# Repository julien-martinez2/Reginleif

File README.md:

# 🕷️ Reginleif — Autonomous Quadruped Walking Robot

[-green.svg)]()

> A custom-engineered, distributed quadruped combat walker inspired by the **XM2 Reginleif** and **M1A4 Juggernaut** from the acclaimed light novel & anime series ***86 - Eighty Six***.

---

## 📖 Table of Contents

- [Motivation & Inspiration](#-motivation--inspiration)
- [System Architecture](#-system-architecture)
  - [Functional Architecture](#functional-architecture)
  - [Technical & Electrical Architecture](#technical--electrical-architecture)
- [Hardware & Key Components](#-hardware--key-components)
  - [Sun Board (Central Controller)](#sun-board)
  - [Planet Boards (Legs Controllers)](#planet-boards)
  - [Moon Boards (Angle Sensors)](#moon-boards)
  - [Dual-Encoder Sensing Strategy](#dual-encoder-sensing-strategy)
- [Firmware Architecture](#-firmware-architecture)
  - [NVIC Preemptive Priority Hierarchy](#nvic-preemptive-priority-hierarchy)
  - [Real-Time Timer Scheduling](#real-time-timer-scheduling)
  - [Zero-CPU UART DMA with IDLE Line Detection](#zero-cpu-uart-dma-with-idle-line-detection)
- [Project Documentation & CAD Assets](#-project-documentation--cad-assets)
- [Roadmap & Deliverables](#-roadmap--deliverables)
- [Author & Community](#-author--community)
- [License](#-license)

---

## 💡 Motivation & Inspiration

The goal of this project is to take the agility, distinctive gait mechanics, and rugged aesthetic of the **XM2 Reginleif** from *86 - Eighty Six* and bring it into physical reality.

Building a multi-jointed legged walker from scratch serves as an end-to-end engineering challenge across multiple disciplines:
1. **Developing Real-Time Embedded Skills:** Mastering bare-metal ARM Cortex-M control, deterministic task scheduling, multi-bus SPI synchronization, and DMA streaming.
2. **Custom PCB & Power Electronics:** Designing compact 4-layer PCBs, handling thermal dissipation, power distribution for 16 simultaneous DC gearmotors, and integrated eFuse circuit protection.
3. **Complex Kinematics & Robotics:** Solving 3D inverse kinematics, gait generation, and closed-loop position control with mechanical backlash compensation.

**Open Source Philosophy:** Advanced quadruped robotics often relies on expensive off-the-shelf smart actuators or proprietary platforms. By documenting every schematic, trade-off, calculation, and line of code, this repository aims to serve as a practical, open reference for robotics students, engineers, and hobbyists building their own legged systems.

---

## 🏛️ System Architecture

### Functional Architecture

The robot employs a **hierarchical distributed architecture**, offloading high-frequency motor control to dedicated microcontrollers while centralizing planning, telemetry, and stabilization:

```
                      ┌────────────────────────────────────────┐
                      │        High-Level Intelligence         │
                      │     Raspberry Pi (Vision, Autonomy)    │
                      └──────────────────┬─────────────────────┘
                                         │ SPI / UART
                                         ▼
                      ┌────────────────────────────────────────┐
                      │    Central Master MCU ("Sun Board")    │
                      │  • IMU Body Stabilization (BNO086)     │
                      │  • Power Distribution & Battery Monitor│
                      │  • Master Gait Coordinator             │
                      └──────────────────┬─────────────────────┘
                                         │
          ┌──────────────────────────────┼──────────────────────────────┐
          │ RS-485 Differential Bus      │ (Master-Slave Protocol)      │
          ▼                              ▼                              ▼
 ┌──────────────────┐           ┌──────────────────┐           ┌──────────────────┐
 │  Planet Board 1  │           │  Planet Board 2  │           │ Planet Boards 3-4│
 │ (STM32G031)      │           │ (STM32G031)      │           │  (STM32G031)     │
 │ 4x N20 Motors    │           │ 4x N20 Motors    │           │ 4x N20 Motors    │
 └──────────────────┘           └──────────────────┘           └──────────────────┘
          │                     SPI Bus  │ (Master-Slave Protocol)      │
          ▼                              ▼                              ▼
 ┌──────────────────┐           ┌──────────────────┐           ┌──────────────────┐
 │ Moon Boards 1-4  │           │ Moon Boards 5-8  │           │ Moon Boards 9-16 │
 │ (MA730 Abs.)     │           │ (MA730 Abs.)     │           │ (MA730 Abs.)     │
 └──────────────────┘           └──────────────────┘           └──────────────────┘

```

---

### Technical & Electrical Architecture

```
                              [ 3S LiPo Battery (11.1V - 12.6V) ]
                                              │
                                              ▼
                                 [ TPS259827 15A eFuse ]
                                (UVLO Cutoff at 10.83V)
                                              │
                  ┌───────────────────────────┼───────────────────────────┐
                  │ VM (12V) Motor Power      │                           │
                  ▼                           ▼                           ▼
        ┌───────────────────┐       ┌───────────────────┐       ┌──────────────────────┐
        │ AP63205 (5V Buck) │       │ AP63203 (3.3V)    │       │ TPS22919 Load SW     │
        │ -> Raspberry Pi   │       │ -> Sun Board MCU  │       │ -> Planet Board VDD  │
        └───────────────────┘       └───────────────────┘       └─────────┬────────────┘
                                                                          │
                                  ┌───────────────────────────────────────┘
                                  │ 5-Pin JST-PA Harness (12V, 3.3V, GND, RS485_A/B)
                                  ▼
         ┌─────────────────────────────────────────────────────────────────┐
         │                     MODULAR PLANET BOARD (x4)                   │
         │                                                                 │
         │   [ THVD1406 RS-485 ] <── UART DMA ──> [ STM32G031 MCU ]        │
         │                                              │                  │
         │              ┌───────────────────────────────┴────────┐         │
         │              ▼ (SPI1 Bus)                             ▼ (SPI2)  │
         │     [ 4x MA730 Encoders ]                       [ DRV8908 ]     │
         │     Absolute Joint Angles                   8x Half-Bridges     │
         │     (Diametric Magnets)                               │         │
         │              ▲                                        ▼         │
         │              │ Joint Output Shaft              4x CHF-GW12T-N20 │
         │              └──────────────────────────────── (302:1 Worm)     │
         │                                                       │         │
         │   [ Incremental Encoders ] <── EXTI (PA0, PB1, PB3, PC14) ─────┘│
         └─────────────────────────────────────────────────────────────────┘

```

---

## 🛠️ Hardware & Key Components

### Sun Board
- **Master Processing:** STM32G031 / Raspberry Pi pairing for autonomous operation, telemetry streaming, and wireless communication.
- **Power & Circuit Protection:**
  - **TPS259827 15A eFuse:** Ultra-fast short-circuit protection and hardware programmable undervoltage lockout (V_UVLO = 10.83 V), preventing 3S LiPo over-discharge).
  - **AP63205 & AP63203:** High-efficiency synchronous buck converters generating 5 V (logic/SBC) and 3.3 V (peripherals).
  - **TPS22919 Load Switches:** Independent hardware-level logic power isolation and current limiting for each peripheral board.
- **Inertial Measurement:** **BNO086** 9-axis sensor fusion IMU over SPI for real-time body attitude stabilization.

### Planet Boards
- **Dedicated MCU:** **STM32G031G8U6** (ARM Cortex-M0+ running at 16 MHz, 4-layer compact layout with solid internal ground planes).
- **Motor Driver:** **DRV8908** automotive-grade 8 half-bridge driver, providing 4 fully independent bi-directional motor channels with individual hardware current limiting and fault telemetry.
- **Bus Transceiver:** **THVD1406DR** RS-485 transceiver with auto-direction sensing, eliminating the need for half-duplex DE/RE switching overhead.
- **Connectors:** JST-PA (power and differential communication) and JST-ZH (motor and sensor interconnects).

### Moon Boards
- **Angle Sensor:** MA730 is a magnetic angle sensor, which is placed next to the shaft of the motor on which a magnet is put.
- **Connectors:** JST-ZH (same as the motors).

---

### Dual-Encoder Sensing Strategy

Miniature worm gearboxes provide high stall torque and self-locking capabilities, but introduce mechanical backlash. To solve this, a dual-encoder feedback architecture is implemented:

| Sensor Type | Part & Interface | Resolution | Placement | Role in Control Loop |
| :--- | :--- | :--- | :--- | :--- |
| **Incremental Magnetic Encoder** | 2-Phase Hall (EXTI) | 2x Quadrature (~2107 counts/rev on motor shaft) | Motor Tail Shaft | **High-frequency velocity estimation** and instantaneous PID rate control. |
| **Absolute Magnetic Encoder** | **MA730GQ-Z** (SPI1) | 14-bit (16,384 counts/rev) | Output Joint Shaft (with Diametric Ring Magnets) | **Absolute angle calibration (10 Hz)** to eliminate gearbox play, backlash, and drift. |

---

## 💻 Firmware Architecture

### NVIC Preemptive Priority Hierarchy

The Cortex-M0+ interrupt controller is prioritized to guarantee that critical hardware signals and high-speed encoder transitions are never delayed by slower math computations:

```

Priority 0 (Highest) ──► SysTick & EXTI Lines (PA0, PB1, PB3, PC14, PA2 nFAULT)
│
Priority 1             ──► USART1 Communication & DMA Channels
│
Priority 2             ──► TIM2 (DRV8908 SPI Updates) & TIM3 (MagAlpha SPI Reads)
│
Priority 3 (Lowest)    ──► TIM1 (Software Inverse Kinematics & PID Loops)

```

- **Zero-Jitter Pulse Counting:** Encoders run at Priority 0 so wheel pulses are captured without dropped ticks during motor acceleration.
- **Fault Handling:** The open-drain `nFAULT` pin on `PA2` triggers an immediate shutdown sequence on overcurrent or thermal warnings.
- **Safe Preemption:** Heavy inverse kinematics floating-point calculations (Priority 3) safely yield execution whenever a peripheral event occurs.

---

### Real-Time Timer Scheduling

| Timer | Execution Frequency | Period | Task Description |
| :--- | :--- | :--- | :--- |
| **EXTI Lines** | Asynchronous | < 1 µs | Hardware edge-triggered incremental encoder decoding (Motors 1–4). |
| **TIM3** | **10 Hz** | 100 ms | SPI1 sequential polling of the 4 joint-level MA730 absolute encoders. |
| **TIM2** | **50 Hz** | 20 ms | SPI2 multi-channel register write updating DRV8908 motor PWM/directions. |
| **TIM1** | **20 Hz - 50 Hz** | 20 - 50 ms | Inverse kinematics trajectory solving, PID position/velocity loop execution. |

---

### Zero-CPU UART DMA with IDLE Line Detection

Communication between the central master board and the leg modules uses DMA combined with hardware IDLE line detection (`HAL_UARTEx_ReceiveToIdle_DMA`):

```cpp
// Non-blocking packet reception
void HAL_UARTEx_RxEventCallback(UART_HandleTypeDef *huart, uint16_t Size) {
    if (huart->Instance == USART1) {
        // Validate header and packet checksum
        if (Size >= 11 && rx_buffer[0] == 0xAA && rx_buffer[1] == 0x55) {
            ParseMasterCommand(rx_buffer, Size);
        }
        // Immediately re-arm DMA reception for the next packet
        HAL_UARTEx_ReceiveToIdle_DMA(&huart1, rx_buffer, RX_BUFFER_SIZE);
    }
}

```

* **Zero CPU overhead** while bytes are on the wire.
* The MCU triggers a single interrupt only after an entire variable-length packet is delivered and the bus goes idle.

---

## 📂 Project Documentation & CAD Assets

All schematics, BOMs, mechanical studies, and test records are available in the repository:

* **Hardware Schematics & KiCad Layouts:** 4-layer Leg Board, Satellite Angle Sensor PCBs, and Central Carrier Board.
* **Mechanical CAD:** 3D printed joint housings, worm gearbox mounts, and chassis brackets.

---

## 🗺️ Roadmap & Deliverables

* [x] Functional specification and torque/power feasibility study
* [x] 4-layer Leg Board PCB design and component assembly (KiCad)
* [ ] Mechanical Design and 3D-printing (FreeCAD)
* [ ] Bare-metal firmware setup (CubeMX, SPI1/SPI2, multi-channel EXTI, UART DMA)
* [ ] MA730 absolute magnetic sensor driver (`magalpha.cpp`)
* [ ] DRV8908 8 half-bridge motor controller driver (`drv8908.cpp`)
* [ ] 3D Inverse Kinematics math library and body orientation matrix
* [ ] Dynamic walking gait generation (Crawl, Trot, and Creep gaits)
* [ ] Central Sun Board assembly & BNO086 IMU stabilization loop
* [ ] Auxiliary subsystems: Tilt-axis turret mechanism and deployable anchor system

---

## 👤 Author & Community

Designed and engineered with passion by **Julien Martinez** ([@julien-martinez2](github.com/julien-martinez2)).

If you are working on custom quadruped walkers, legged robotics, or distributed motor controllers, feel free to open an issue, start a discussion, or contribute!

---

## 📄 License

This project is distributed under the **MIT License**. See [`LICENSE`](https://www.google.com/search?q=LICENSE) for more details.

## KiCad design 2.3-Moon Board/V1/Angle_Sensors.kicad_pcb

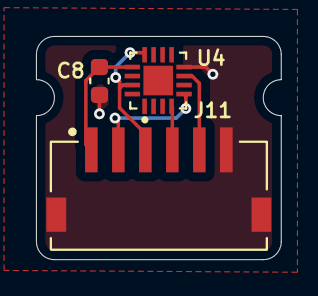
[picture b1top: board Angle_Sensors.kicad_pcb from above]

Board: 4 copper layers, 13.6 x 12.4 mm, 3 parts (0 on the bottom side), 6 nets.

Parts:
C8: 1uF; C_0603_1608Metric
J11: S6B-ZR-SM4-TF; JST_S6B-ZR-SM4A-TF_LF__SN_
U4: MA730GQ-Z_1; QFN50P300X300X100-17N

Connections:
+3.3V: C8.1, J11.1, U4.13 (VDD)
GND: C8.2, J11.6, J11.SH1 (SHIELD), J11.SH2 (SHIELD), U4.8 (GND)
unnamed: J11.2, U4.5 (CS)
unnamed: J11.5, U4.7 (MISO)
unnamed: J11.4, U4.4 (MOSI)
unnamed: J11.3, U4.12 (SCLK), U4.15 (SSCK)

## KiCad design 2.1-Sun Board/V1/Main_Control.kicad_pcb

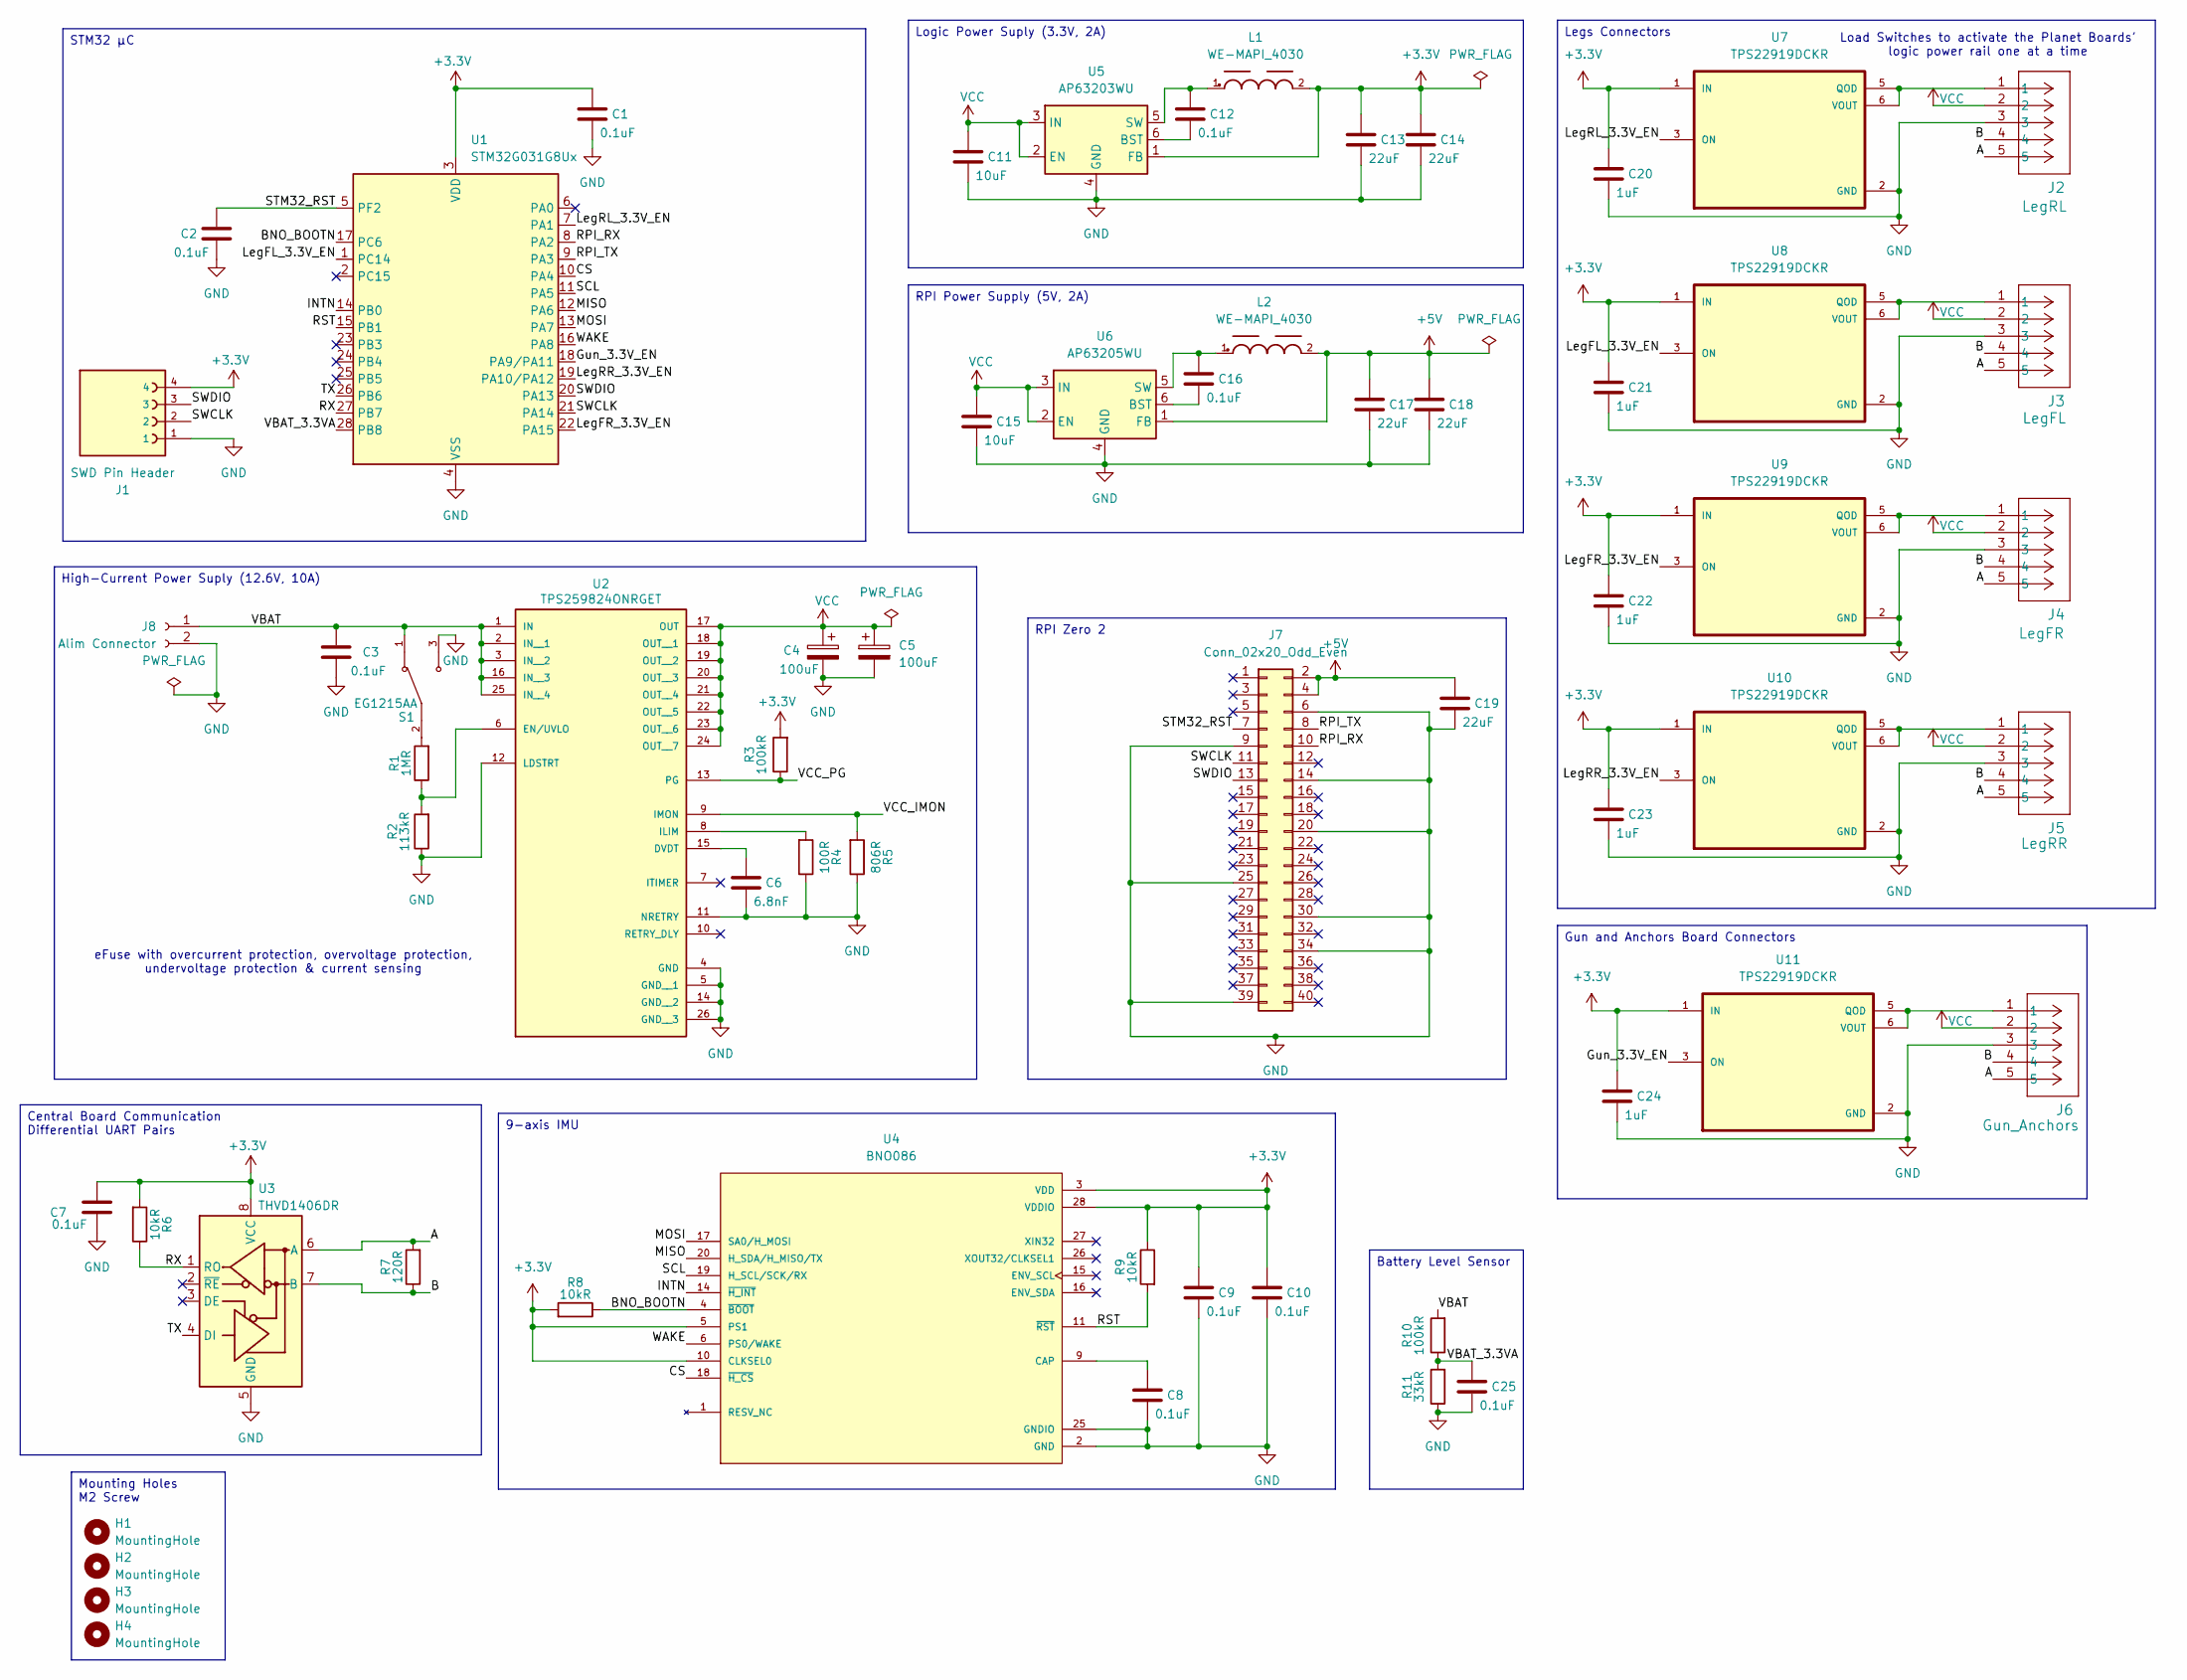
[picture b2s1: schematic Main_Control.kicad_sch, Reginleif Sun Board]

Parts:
C1, C2, C3, C7, C8, C9, C10, C12, C16, C25: 0.1uF; C_0603_1608Metric
C4, C5: 100uF; CP_EIA-7343-43_Kemet-X
C6: 6.8nF; C_0402_1005Metric
C11, C15: 10uF; C_0603_1608Metric
C13, C14, C17, C18: 22uF; C_0805_2012Metric
C19: 22uF; R_0805_2012Metric
C20, C21, C22, C23, C24: 1uF; C_0402_1005Metric
H1, H2, H3, H4: MountingHole; MountingHole_2.2mm_M2
J1: SWD Pin Header; HARWIN_M20-7910442R
J2: LegRL; SM05B_PASS
J3: LegFL; SM05B_PASS
J4: LegFR; SM05B_PASS
J5: LegRR; SM05B_PASS
J6: Gun_Anchors; SM05B_PASS
J7: Conn_02x20_Odd_Even; PinHeader_2x20_P2.54mm_Vertical_SMD
J8: Alim Connector; SolderWire-0.75sqmm_1x02_P4.8mm_D1.25mm_OD2.3mm_Relief
L1, L2: WE-MAPI_4030
R1: 1MR; R_0402_1005Metric
R2: 113kR; R_0402_1005Metric
R3, R10: 100kR; R_0402_1005Metric
R4: 100R; R_0402_1005Metric
R5: 806R; R_0402_1005Metric
R6, R8, R9: 10kR; R_0603_1608Metric
R7: 120R; R_0402_1005Metric
R11: 33kR; R_0402_1005Metric
S1: EG1215AA; SW_EG1215AA; PARTREV A
U1: STM32G031G8Ux; QFN-28_4x4mm_P0.5mm
U2: TPS259824ONRGET; IC_TPS259824ONRGET; Part_Rev C
U3: THVD1406DR; SOIC-8_3.9x4.9mm_P1.27mm
U4: BNO086; IC_BNO086; PARTREV v1.17
U5: AP63203WU; TSOT-23-6
U6: AP63205WU; TSOT-23-6
U7, U8, U9, U10, U11: TPS22919DCKR; SOT65P210X110-6N

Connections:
+3.3V: C1.1, C7.1, C9.1, C10.1, C13.1, C14.1, C20.1, C21.1, C22.1, C23.1, C24.1, J1.4, L1.2, R3.2, R6.2, R8.2, R9.1, U1.3 (VDD), U3.8 (VCC), U4.3 (VDD), U4.5 (PS1), U4.10 (CLKSEL0), U4.28 (VDDIO), U5.1 (FB), U7.1 (IN), U8.1 (IN), U9.1 (IN), U10.1 (IN), U11.1 (IN)
+5V: C17.1, C18.1, C19.1, J7.2, J7.4, L2.2, U6.1 (FB)
/A: J2.5, J3.5, J4.5, J5.5, J6.5, R7.2, U3.6 (A)
/B: J2.4, J3.4, J4.4, J5.4, J6.4, R7.1, U3.7 (B)
/BNO_BOOTN: R8.1, U1.17 (PC6), U4.4 (~BOOT)
/CS: U1.10 (PA4), U4.18 (~H_CS)
/Gun_3.3V_EN: U1.18 (PA9/PA11), U11.3 (ON)
/INTN: U1.14 (PB0), U4.14 (~H_INT)
/LegFL_3.3V_EN: U1.1 (PC14), U8.3 (ON)
/LegFR_3.3V_EN: U1.22 (PA15), U9.3 (ON)
/LegRL_3.3V_EN: U1.7 (PA1), U7.3 (ON)
/LegRR_3.3V_EN: U1.19 (PA10/PA12), U10.3 (ON)
/MISO: U1.12 (PA6), U4.20 (H_SDA/H_MISO/TX)
/MOSI: U1.13 (PA7), U4.17 (SA0/H_MOSI)
/RPI_RX: J7.10, U1.8 (PA2)
/RPI_TX: J7.8, U1.9 (PA3)
/RST: R9.2, U1.15 (PB1), U4.11 (~RST)
/RX: R6.1, U1.27 (PB7), U3.1 (RO)
/SCL: U1.11 (PA5), U4.19 (H_SCL/SCK/RX)
/STM32_RST: C2.1, J7.7, U1.5 (PF2)
/SWCLK: J1.2, J7.11, U1.21 (PA14)
/SWDIO: J1.3, J7.13, U1.20 (PA13)
/TX: U1.26 (PB6), U3.4 (DI)
/VBAT: C3.1, J8.1, R10.2, S1.1, U2.1 (IN), U2.2 (IN__1), U2.3 (IN__2), U2.16 (IN__3), U2.25 (IN__4), U2.27, U2.28, U2.29, U2.30, U2.31, U2.32
/VBAT_3.3VA: C25.1, R10.1, R11.2, U1.28 (PB8)
/VCC_IMON: R5.2, U2.9 (IMON)
/VCC_PG: R3.1, U2.13 (PG)
/WAKE: U1.16 (PA8), U4.6 (PS0/WAKE)
GND: C1.2, C2.2, C3.2, C4.2, C5.2, C6.2, C7.2, C8.2, C9.2, C10.2, C11.2, C13.2, C14.2, C15.2, C17.2, C18.2, C19.2, C20.2, C21.2, C22.2, C23.2, C24.2, C25.2, J1.1, J2.3, J3.3, J4.3, J5.3, J6.3, J7.6, J7.9, J7.14, J7.20, J7.25, J7.30, J7.34, J7.39, J8.2, R2.1, R4.1, R5.1, R11.1, S1.3, U1.4 (VSS), U2.4 (GND), U2.5 (GND__1), U2.11 (NRETRY), U2.12 (LDSTRT), U2.14 (GND__2), U2.26 (GND__3), U2.33, U2.34, U2.35, U3.5 (GND), U4.2 (GND), U4.25 (GNDIO), U5.4 (GND), U6.4 (GND), U7.2 (GND), U8.2 (GND), U9.2 (GND), U10.2 (GND), U11.2 (GND)
unnamed: R1.2, S1.2
unnamed: C6.1, U2.15 (DVDT)
unnamed: R1.1, R2.2, U2.6 (EN/UVLO)
unnamed: R4.2, U2.8 (ILIM)
unnamed: C8.1, U4.9 (CAP)
unnamed: C12.2, U5.6 (BST)
unnamed: C12.1, L1.1, U5.5 (SW)
unnamed: C16.2, U6.6 (BST)
unnamed: C16.1, L2.1, U6.5 (SW)
unnamed: J2.1, U7.5 (QOD), U7.6 (VOUT)
unnamed: J3.1, U8.5 (QOD), U8.6 (VOUT)
unnamed: J4.1, U9.5 (QOD), U9.6 (VOUT)
unnamed: J5.1, U10.5 (QOD), U10.6 (VOUT)
unnamed: J6.1, U11.5 (QOD), U11.6 (VOUT)
VCC: C4.1, C5.1, C11.1, C15.1, J2.2, J3.2, J4.2, J5.2, J6.2, U2.17 (OUT), U2.18 (OUT__1), U2.19 (OUT__2), U2.20 (OUT__3), U2.21 (OUT__4), U2.22 (OUT__5), U2.23 (OUT__6), U2.24 (OUT__7), U5.2 (EN), U5.3 (IN), U6.2 (EN), U6.3 (IN)

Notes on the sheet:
Load Switches to activate the Planet Boards' logic power rail one at a time
eFuse with overcurrent protection, overvoltage protection, undervoltage protection & current sensing
STM32 µC
RPI Power Supply (5V, 2A)
Legs Connectors
Mounting Holes M2 Screw
Gun and Anchors Board Connectors
Logic Power Suply (3.3V, 2A)
Central Board Communication Differential UART Pairs
9-axis IMU
High-Current Power Suply (12.6V, 10A)
Battery Level Sensor
RPI Zero 2

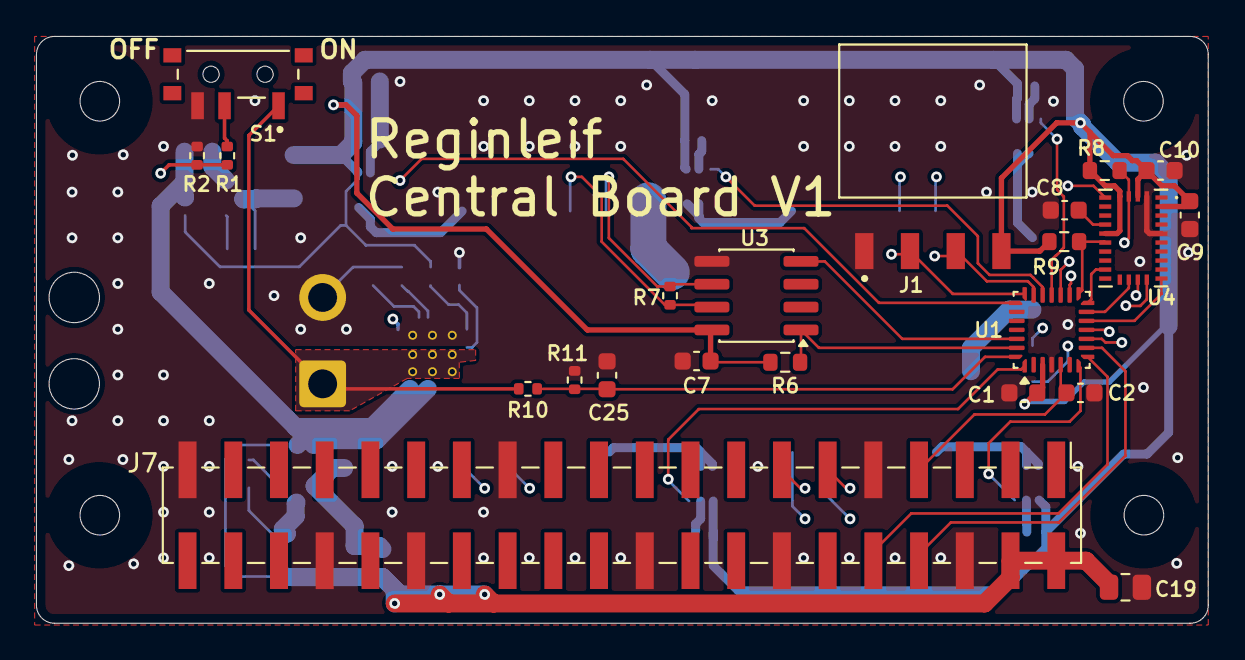
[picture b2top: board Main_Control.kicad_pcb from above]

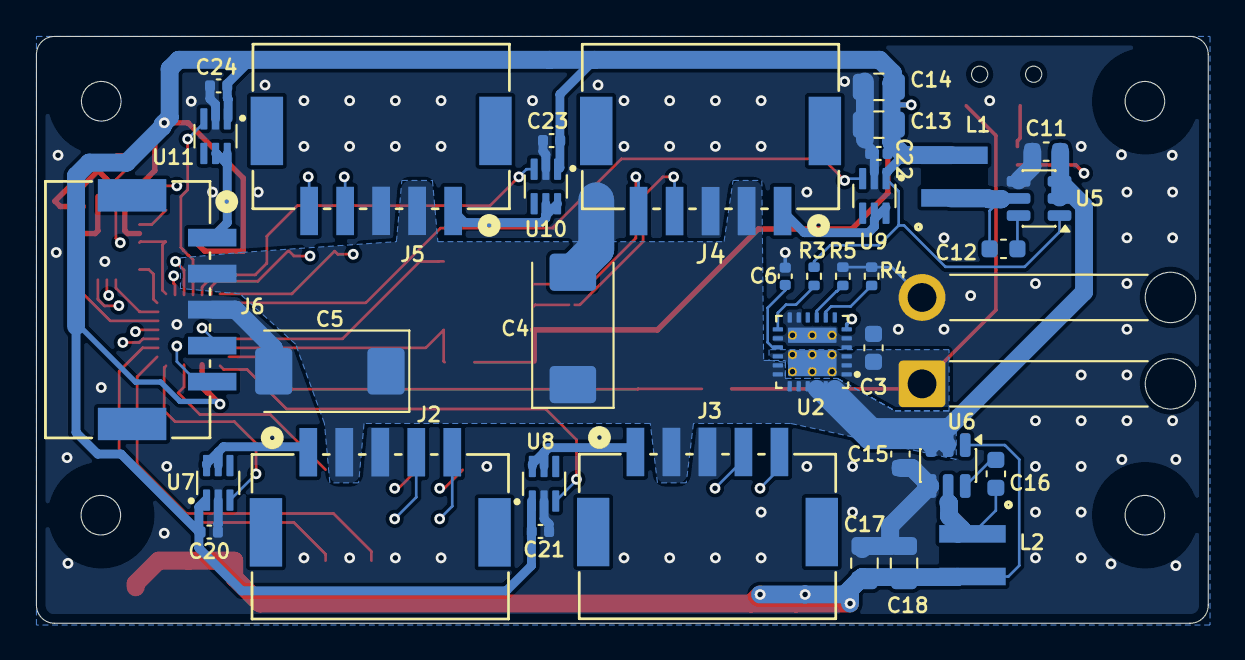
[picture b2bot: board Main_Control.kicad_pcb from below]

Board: 4 copper layers, 65.1 x 32.6 mm, 62 parts (36 on the bottom side), 44 nets.

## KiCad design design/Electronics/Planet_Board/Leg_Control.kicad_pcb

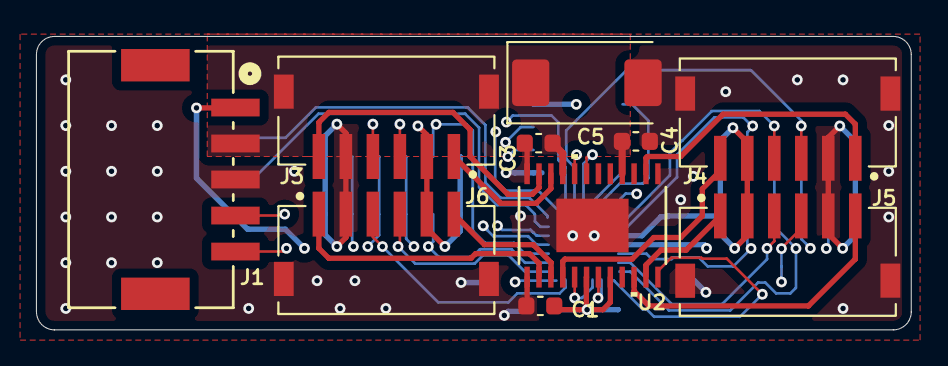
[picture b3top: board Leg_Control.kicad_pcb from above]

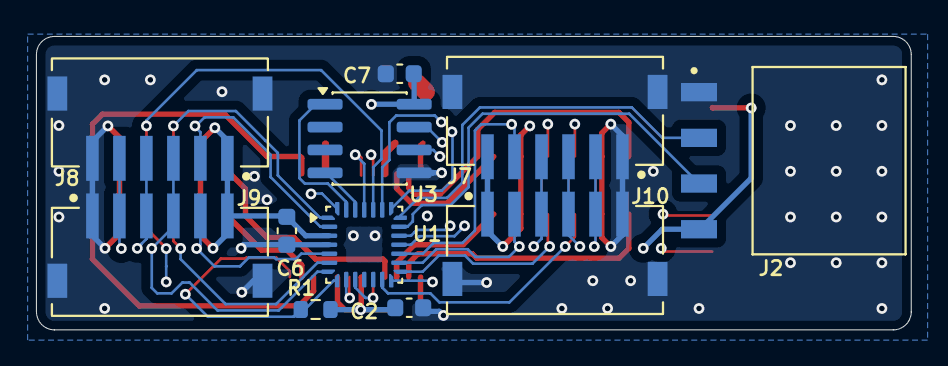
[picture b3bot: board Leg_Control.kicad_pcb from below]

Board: 4 copper layers, 48.6 x 16.3 mm, 21 parts (11 on the bottom side), 37 nets.

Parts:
C1: 1uF; C_0603_1608Metric
C2, C3, C4, C6, C7: 0.1uF; C_0603_1608Metric
C5: 100uF; CP_EIA-7343-43_Kemet-X
J1: SM05B-PASS-TBT; SM05B_PASS
J2: SWD Pin Header; HARWIN_M20-7910442R
J3: Motor_1; JST_S6B-ZR-SM4A-TF_LF__SN_
J4: Motor_2; JST_S6B-ZR-SM4A-TF_LF__SN_
J5: Motor_3; JST_S6B-ZR-SM4A-TF_LF__SN_
J6: Motor_4; JST_S6B-ZR-SM4A-TF_LF__SN_
J7: MagAlpha_1; JST_S6B-ZR-SM4A-TF_LF__SN_
J8: MagAlpha_2; JST_S6B-ZR-SM4A-TF_LF__SN_
J9: MagAlpha_3; JST_S6B-ZR-SM4A-TF_LF__SN_
J10: MagAlpha_4; JST_S6B-ZR-SM4A-TF_LF__SN_
R1: 10kR; R_0603_1608Metric
U1: STM32G031G8Ux; QFN-28_4x4mm_P0.5mm
U2: DRV8908QPWPRQ1; PWP24_4P5X7P9_TEX-L
U3: THVD1406DR; SOIC-8_3.9x4.9mm_P1.27mm

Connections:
+3.3V: C1.1, C2.1, C6.1, C7.1, J1.1, J2.4, J3.2, J4.5, J5.2, J6.5, J7.6, J8.1, J9.6, J10.1, R1.1, U1.3 (VDD), U2.6 (VDD), U2.8 (NSLEEP), U3.8 (VCC)
/A: J1.5, U3.6 (A)
/B: J1.4, U3.7 (B)
/E_A_1: J3.4, U1.22 (PA15)
/E_A_2: J4.3, U1.24 (PB4)
/E_A_3: J5.4, U1.14 (PB0)
/E_A_4: J6.3, U1.13 (PA7)
/E_B_1: J3.3, U1.23 (PB3)
/E_B_2: J4.4, U1.1 (PC14)
/E_B_3: J5.3, U1.6 (PA0)
/E_B_4: J6.4, U1.15 (PB1)
/M1_1: J3.6, U2.23 (OUT2)
/M1_2: J3.1, U2.22 (OUT8)
/M2_1: J4.1, U2.14 (OUT3)
/M2_2: J4.6, U2.4 (OUT7)
/M3_1: J5.6, U2.10 (OUT6)
/M3_2: J5.1, U2.11 (OUT4)
/M4_1: J6.1, U2.2 (OUT1)
/M4_2: J6.6, U2.3 (OUT5)
/NFAULT: R1.2, U1.8 (PA2), U2.12 (NFAULT)
/RX: U1.27 (PB7), U3.1 (RO)
/SPI1_CS_1: J7.5, U1.17 (PC6)
/SPI1_CS_2: J8.2, U1.2 (PC15)
/SPI1_CS_3: J9.5, U1.5 (PF2)
/SPI1_CS_4: J10.2, U1.16 (PA8)
/SPI1_MISO: J7.2, J8.5, J9.2, J10.5, U1.18 (PA9/PA11)
/SPI1_MOSI: J7.3, J8.4, J9.3, J10.4, U1.19 (PA10/PA12)
/SPI1_SCK: J7.4, J8.3, J9.4, J10.3, U1.7 (PA1)
/SPI2_CS: U1.25 (PB5), U2.19 (NSCS)
/SPI2_MISO: U1.9 (PA3), U2.7 (SDO)
/SPI2_MOSI: U1.10 (PA4), U2.5 (SDI)
/SPI2_SCK: U1.28 (PB8), U2.20 (SCLK)
/SWCLK: J2.2, U1.21 (PA14)
/SWDIO: J2.3, U1.20 (PA13)
/TX: U1.26 (PB6), U3.4 (DI)
GND: C1.2, C2.2, C3.2, C4.2, C5.2, C6.2, C7.2, J1.3, J2.1, J3.5, J4.2, J4.SH1 (SHIELD), J4.SH2 (SHIELD), J5.5, J5.SH1 (SHIELD), J5.SH2 (SHIELD), J6.2, J6.SH1 (SHIELD), J6.SH2 (SHIELD), J7.1, J7.SH1 (SHIELD), J7.SH2 (SHIELD), J8.6, J8.SH1 (SHIELD), J8.SH2 (SHIELD), J9.1, J9.SH1 (SHIELD), J9.SH2 (SHIELD), J10.6, J10.SH1 (SHIELD), J10.SH2 (SHIELD), U1.4 (VSS), U2.1 (GND), U2.13 (GND), U2.24 (GND), U2.EPAD, U3.5 (GND)
VCC: C3.1, C4.1, C5.1, J1.2, J3.SH1 (SHIELD), J3.SH2 (SHIELD), U2.16 (VM), U2.21 (VM)

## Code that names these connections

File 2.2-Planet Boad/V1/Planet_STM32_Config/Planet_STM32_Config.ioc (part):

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Mcu.Name=STM32G031G(4-6-8)Ux
Mcu.Package=UFQFPN28
Mcu.UserName=STM32G031G8Ux
PA0.GPIOParameters=GPIO_PuPd,GPIO_Label
PA0.GPIO_Label=E_3_B
PA0.GPIO_PuPd=GPIO_PULLUP
PA0.Signal=GPXTI0
PA1.Mode=Full_Duplex_Master
PA1.Signal=SPI1_SCK
PA11\ [PA9].Mode=Full_Duplex_Master
PA11\ [PA9].Signal=SPI1_MISO
PA12\ [PA10].Mode=Full_Duplex_Master
PA12\ [PA10].Signal=SPI1_MOSI
PA13.Mode=Serial_Wire
PA13.Signal=SYS_SWDIO
PA14-BOOT0.Mode=Serial_Wire
PA14-BOOT0.Signal=SYS_SWCLK
PA15.GPIOParameters=GPIO_PuPd,GPIO_Label
PA15.GPIO_Label=E_1_A
PA15.GPIO_PuPd=GPIO_PULLUP
PA15.Signal=GPIO_Input
PA2.GPIOParameters=GPIO_Label,GPIO_ModeDefaultEXTI
PA2.GPIO_Label=NFAULT
PA2.GPIO_ModeDefaultEXTI=GPIO_MODE_IT_FALLING
PA2.Signal=GPXTI2
PA3.Mode=Full_Duplex_Master
PA3.Signal=SPI2_MISO
PA4.Mode=Full_Duplex_Master
PA4.Signal=SPI2_MOSI
PA7.GPIOParameters=GPIO_PuPd,GPIO_Label
PA7.GPIO_Label=E_4_A
PA7.GPIO_PuPd=GPIO_PULLUP
PA7.Signal=GPIO_Input
PA8.GPIOParameters=GPIO_Speed,PinState,GPIO_Label
PA8.GPIO_Label=SPI1_CS_4
PA8.GPIO_Speed=GPIO_SPEED_FREQ_VERY_HIGH
PA8.PinState=GPIO_PIN_SET
PA8.Signal=GPIO_Output
PB0.GPIOParameters=GPIO_PuPd,GPIO_Label
PB0.GPIO_Label=E_3_A
PB0.GPIO_PuPd=GPIO_PULLUP
PB0.Signal=GPIO_Input
PB1.GPIOParameters=GPIO_PuPd,GPIO_Label
PB1.GPIO_Label=E_4_B
PB1.GPIO_PuPd=GPIO_PULLUP
PB1.Signal=GPXTI1
PB3.GPIOParameters=GPIO_PuPd,GPIO_Label
PB3.GPIO_Label=E_1_B
PB3.GPIO_PuPd=GPIO_PULLUP
PB3.Signal=GPXTI3
PB4.GPIOParameters=GPIO_PuPd,GPIO_Label
PB4.GPIO_Label=E_2_A
PB4.GPIO_PuPd=GPIO_PULLUP
PB4.Signal=GPIO_Input
PB5.GPIOParameters=GPIO_Speed,PinState,GPIO_Label
PB5.GPIO_Label=SPI2_CS
PB5.GPIO_Speed=GPIO_SPEED_FREQ_VERY_HIGH
PB5.PinState=GPIO_PIN_SET
PB5.Signal=GPIO_Output
PB6.GPIOParameters=GPIO_Speed
PB6.GPIO_Speed=GPIO_SPEED_FREQ_HIGH
PB6.Mode=Asynchronous
PB6.Signal=USART1_TX
PB7.GPIOParameters=GPIO_PuPd
PB7.GPIO_PuPd=GPIO_PULLUP
PB7.Mode=Asynchronous
PB7.Signal=USART1_RX
PB8.Mode=Full_Duplex_Master
PB8.Signal=SPI2_SCK
PC14-OSC32_IN\ (PC14).GPIOParameters=GPIO_PuPd,GPIO_Label
PC14-OSC32_IN\ (PC14).GPIO_Label=E_2_B
PC14-OSC32_IN\ (PC14).GPIO_PuPd=GPIO_PULLUP
PC14-OSC32_IN\ (PC14).Signal=GPXTI14
PC15-OSC32_OUT\ (PC15).GPIOParameters=PinState,GPIO_Label
PC15-OSC32_OUT\ (PC15).GPIO_Label=SPI1_CS_2
PC15-OSC32_OUT\ (PC15).PinState=GPIO_PIN_SET
PC15-OSC32_OUT\ (PC15).Signal=GPIO_Output
PC6.GPIOParameters=GPIO_Speed,PinState,GPIO_Label
PC6.GPIO_Label=SPI1_CS_1
PC6.GPIO_Speed=GPIO_SPEED_FREQ_VERY_HIGH
PC6.PinState=GPIO_PIN_SET
PC6.Signal=GPIO_Output
PF2\ -\ NRST.GPIOParameters=GPIO_Speed,PinState,GPIO_Label
PF2\ -\ NRST.GPIO_Label=SPI1_CS_3
PF2\ -\ NRST.GPIO_Speed=GPIO_SPEED_FREQ_VERY_HIGH
PF2\ -\ NRST.PinState=GPIO_PIN_SET
PF2\ -\ NRST.Signal=GPIO_Output
RCC.HSE_VALUE=8000000
RCC.SYSCLKFreq_VALUE=16000000
board=custom

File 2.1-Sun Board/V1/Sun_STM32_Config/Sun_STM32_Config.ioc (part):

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Mcu.Name=STM32G031G(4-6-8)Ux
Mcu.Package=UFQFPN28
Mcu.UserName=STM32G031G8Ux
PA13.Mode=Serial_Wire
PA13.Signal=SYS_SWDIO
PA14-BOOT0.Mode=Serial_Wire
PA14-BOOT0.Signal=SYS_SWCLK
PA2.Mode=Asynchronous
PA2.Signal=USART2_TX
PA3.Mode=Asynchronous
PA3.Signal=USART2_RX
PA4.Mode=NSS_Signal_Hard_Output
PA4.Signal=SPI1_NSS
PA5.Mode=Full_Duplex_Master
PA5.Signal=SPI1_SCK
PA6.Mode=Full_Duplex_Master
PA6.Signal=SPI1_MISO
PA7.Mode=Full_Duplex_Master
PA7.Signal=SPI1_MOSI
PB6.Mode=Asynchronous
PB6.Signal=USART1_TX
PB7.Mode=Asynchronous
PB7.Signal=USART1_RX
PB8.Signal=GPIO_Analog
PF2\ -\ NRST.Signal=GPIO_Input
RCC.HSE_VALUE=8000000
RCC.SYSCLKFreq_VALUE=16000000
board=custom

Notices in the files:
README.md:
License: MIT
